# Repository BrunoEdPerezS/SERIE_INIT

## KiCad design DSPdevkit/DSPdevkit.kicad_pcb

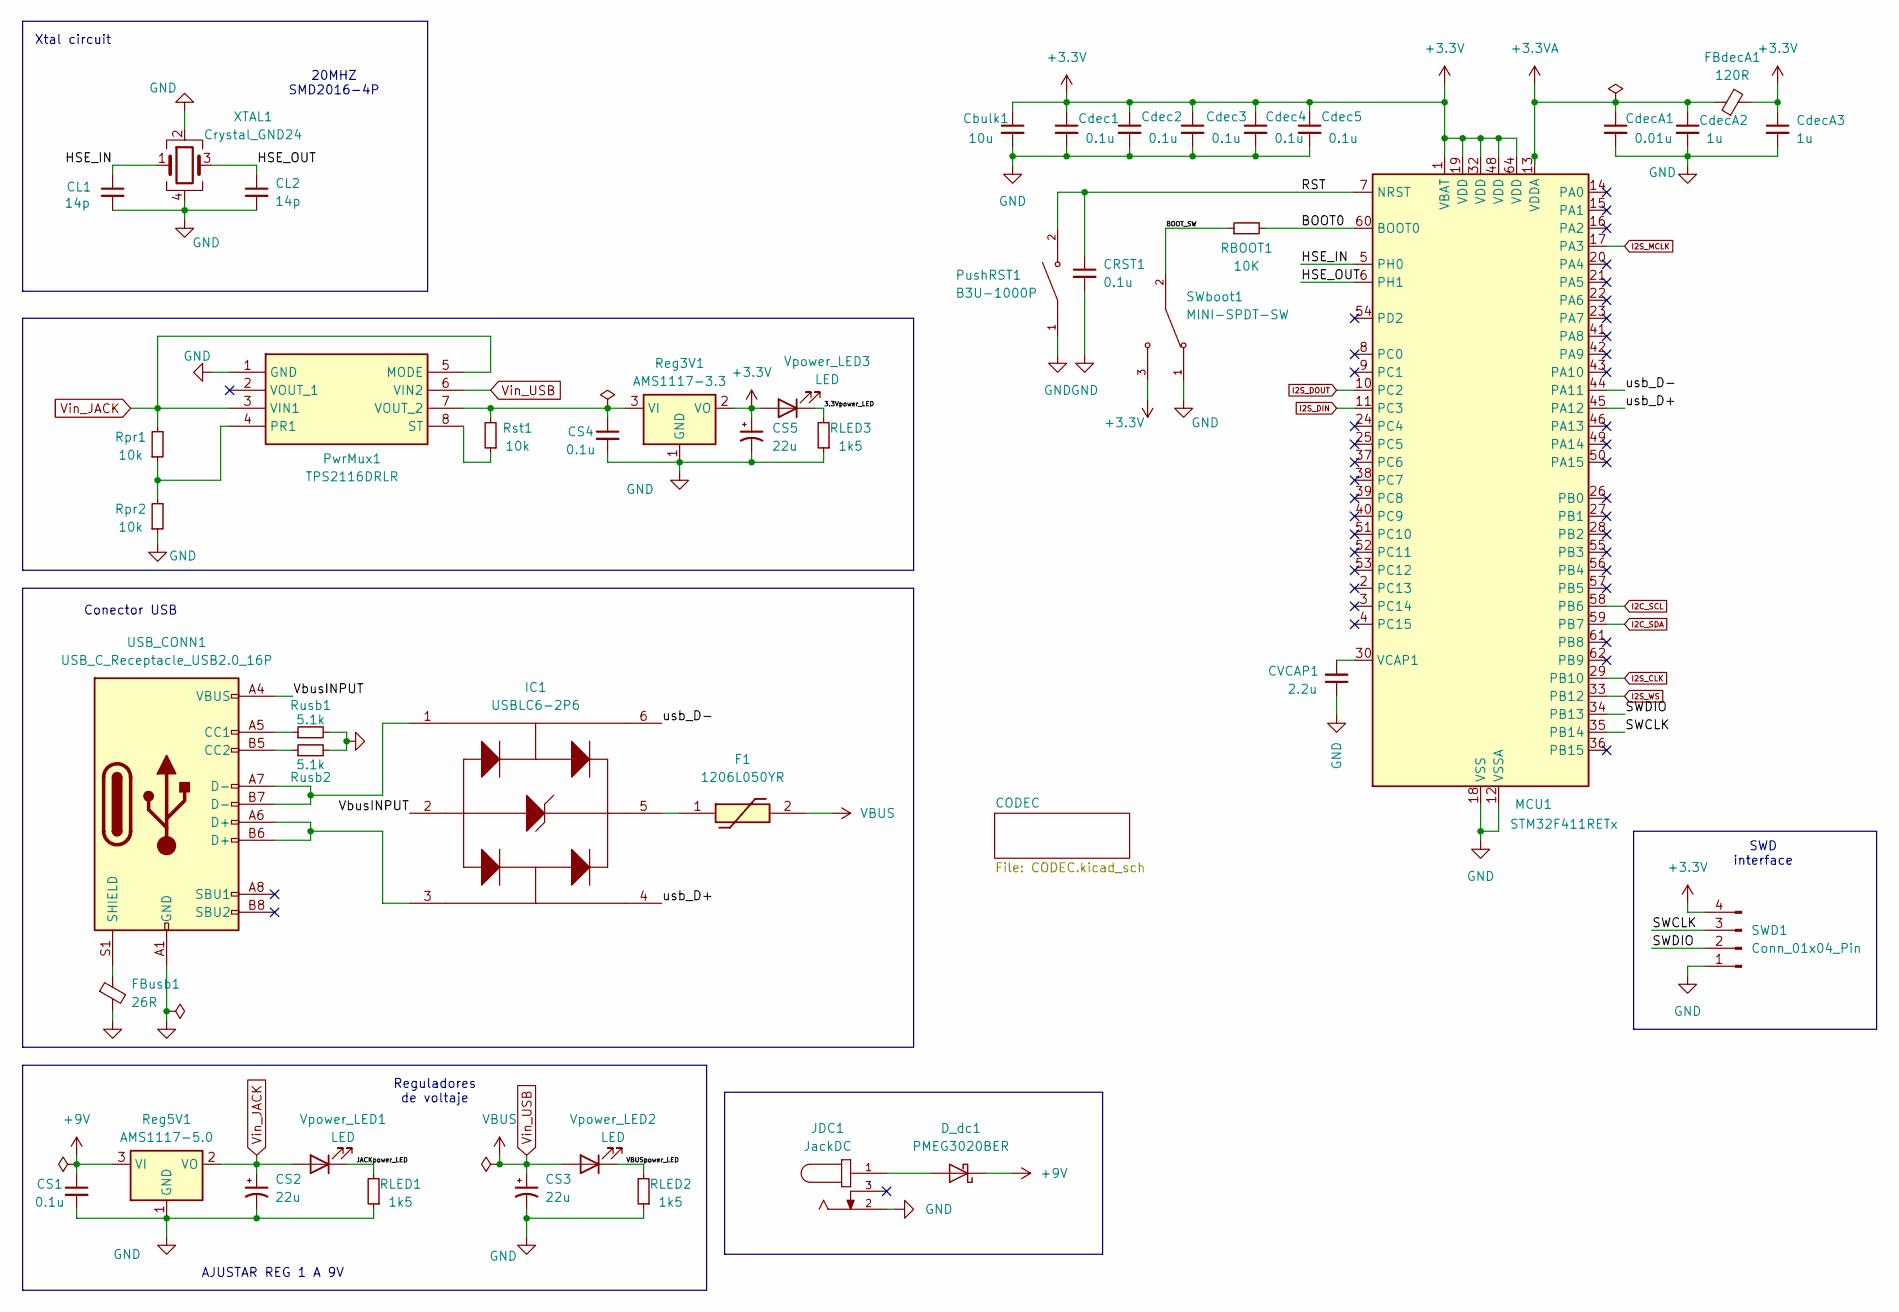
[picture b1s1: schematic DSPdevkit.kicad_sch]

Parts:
CL1, CL2: 14p; C_0402_1005Metric_Pad0.74x0.62mm_HandSolder
CRST1: 0.1u; C_0402_1005Metric_Pad0.74x0.62mm_HandSolder
CS1, CS4: 0.1u; C_1206_3216Metric_Pad1.33x1.80mm_HandSolder
CS2, CS3, CS5: 22u; CP_Elec_6.3x5.4
CVCAP1: 2.2u; C_1206_3216Metric_Pad1.33x1.80mm_HandSolder
Cbulk1: 10u; C_0805_2012Metric_Pad1.18x1.45mm_HandSolder
Cdec1, Cdec2, Cdec3, Cdec4, Cdec5: 0.1u; C_0402_1005Metric_Pad0.74x0.62mm_HandSolder
CdecA1: 0.01u; C_0402_1005Metric_Pad0.74x0.62mm_HandSolder
CdecA2, CdecA3: 1u; C_0402_1005Metric_Pad0.74x0.62mm_HandSolder
D_dc1: PMEG3020BER; Nexperia_CFP3_SOD-123W
F1: 1206L050YR; 1206L05015YR; Mouser Part Number 576-1206L050YR
FBdecA1: 120R; L_0603_1608Metric_Pad1.05x0.95mm_HandSolder
FBusb1: 26R; L_0603_1608Metric_Pad1.05x0.95mm_HandSolder
IC1: USBLC6-2P6; USBLC62P6; Mouser Part Number 511-USBLC6-2P6
JDC1: JackDC; GCT_DCJ200-10-A-XX-K_REVA; PARTREV A
MCU1: STM32F411RETx; LQFP-64_10x10mm_P0.5mm
PushRST1: B3U-1000P; SW_SPST_B3U-1000P
PwrMux1: TPS2116DRLR; SOTFL50P160X60-8N; Mouser Part Number 595-TPS2116DRLR
RBOOT1: 10K; R_1206_3216Metric_Pad1.30x1.75mm_HandSolder
RLED1, RLED2, RLED3: 1k5; R_1206_3216Metric_Pad1.30x1.75mm_HandSolder
Reg3V1: AMS1117-3.3; SOT-223-3_TabPin2
Reg5V1: AMS1117-5.0; SOT-223-3_TabPin2
Rpr1, Rpr2: 10k; R_1206_3216Metric_Pad1.30x1.75mm_HandSolder
Rst1: 10k; R_1206_3216Metric_Pad1.30x1.75mm_HandSolder
Rusb1, Rusb2: 5.1k; R_1206_3216Metric_Pad1.30x1.75mm_HandSolder
SWD1: Conn_01x04_Pin; PinHeader_1x04_P1.00mm_Vertical
SWboot1: MINI-SPDT-SW; SW_MINI-SPDT-SW; PARTREV C
USB_CONN1: USB_C_Receptacle_USB2.0_16P; USB_C_Receptacle_GCT_USB4105-xx-A_16P_TopMnt_Horizontal
Vpower_LED1, Vpower_LED2, Vpower_LED3: LED; LED_1206_3216Metric_Pad1.42x1.75mm_HandSolder
XTAL1: Crystal_GND24; Crystal_SMD_2016-4Pin_2.0x1.6mm

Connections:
+3.3V: CS5.1, Cbulk1.1, Cdec1.1, Cdec2.1, Cdec3.1, Cdec4.1, Cdec5.1, CdecA3.1, FBdecA1.2, MCU1.1 (VBAT), MCU1.19 (VDD), MCU1.32 (VDD), MCU1.48 (VDD), MCU1.64 (VDD), Reg3V1.2 (VO), SWD1.4, SWboot1.3, Vpower_LED3.2 (A); also elsewhere on the board
+3.3VA: CdecA1.1, CdecA2.1, FBdecA1.1, MCU1.13 (VDDA)
+9V: CS1.1, D_dc1.1 (K), Reg5V1.3 (VI)
/3.3Vpower_LED: RLED3.2, Vpower_LED3.1 (K)
/BOOT0: MCU1.60 (BOOT0), RBOOT1.2
/BOOT_SW: RBOOT1.1, SWboot1.2
/HSE_IN: CL1.1, MCU1.5 (PH0), XTAL1.1
/HSE_OUT: CL2.1, MCU1.6 (PH1), XTAL1.3
/JACKpower_LED: RLED1.2, Vpower_LED1.1 (K)
/RST: CRST1.1, MCU1.7 (NRST), PushRST1.2
/SWCLK: MCU1.35 (PB14), SWD1.3
/SWDIO: MCU1.34 (PB13), SWD1.2
/VBUSpower_LED: RLED2.2, Vpower_LED2.1 (K)
/VbusINPUT: IC1.2 (GND), USB_CONN1.A4 (VBUS), USB_CONN1.A9 (VBUS), USB_CONN1.B4 (VBUS), USB_CONN1.B9 (VBUS)
/usb_D+: IC1.4 (I/O2_2), MCU1.45 (PA12)
/usb_D-: IC1.6 (I/O1_2), MCU1.44 (PA11)
GND: CL1.2, CL2.2, CRST1.2, CS1.2, CS2.2, CS3.2, CS4.2, CS5.2, CVCAP1.1, Cbulk1.2, Cdec1.2, Cdec2.2, Cdec3.2, Cdec4.2, Cdec5.2, CdecA1.2, CdecA2.2, CdecA3.2, FBusb1.2, JDC1.2, MCU1.12 (VSSA), MCU1.18 (VSS), MCU1.31 (VSS), MCU1.47 (VSS), MCU1.63 (VSS), PushRST1.1, PwrMux1.1 (GND), RLED1.1, RLED2.1, RLED3.1, Reg3V1.1 (GND), Reg5V1.1 (GND), Rpr2.1, Rusb1.2, Rusb2.2, SWD1.1, SWboot1.1, USB_CONN1.A1 (GND), USB_CONN1.A12 (GND), USB_CONN1.B1 (GND), USB_CONN1.B12 (GND), XTAL1.2, XTAL1.4; also elsewhere on the board
I2C_SCL: MCU1.58 (PB6); also elsewhere on the board
I2C_SDA: MCU1.59 (PB7); also elsewhere on the board
I2S_CLK: MCU1.29 (PB10); also elsewhere on the board
I2S_DIN: MCU1.11 (PC3); also elsewhere on the board
I2S_DOUT: MCU1.10 (PC2); also elsewhere on the board
I2S_MCLK: MCU1.17 (PA3); also elsewhere on the board
I2S_WS: MCU1.33 (PB12); also elsewhere on the board
unnamed: D_dc1.2 (A), JDC1.1
unnamed: IC1.1 (I/O1_1), USB_CONN1.A7 (D-), USB_CONN1.B7 (D-)
unnamed: IC1.3 (I/O2_1), USB_CONN1.A6 (D+), USB_CONN1.B6 (D+)
unnamed: F1.1, IC1.5 (VBUS)
unnamed: CVCAP1.2, MCU1.30 (VCAP1)
unnamed: PwrMux1.4 (PR1), Rpr1.1, Rpr2.2
unnamed: PwrMux1.8 (ST), Rst1.1
unnamed: CS4.1, PwrMux1.7 (VOUT_2), Reg3V1.3 (VI), Rst1.2
unnamed: Rusb1.1, USB_CONN1.A5 (CC1)
unnamed: Rusb2.1, USB_CONN1.B5 (CC2)
unnamed: FBusb1.1, USB_CONN1.S1 (SHIELD)
Vin_JACK: CS2.1, PwrMux1.3 (VIN1), PwrMux1.5 (MODE), Reg5V1.2 (VO), Rpr1.2, Vpower_LED1.2 (A)
Vin_USB: CS3.1, F1.2, PwrMux1.6 (VIN2), Vpower_LED2.2 (A)

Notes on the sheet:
Conector USB
Xtal circuit
Reguladores de voltaje
SWD interface
AJUSTAR REG 1 A 9V
20MHZ SMD2016-4P

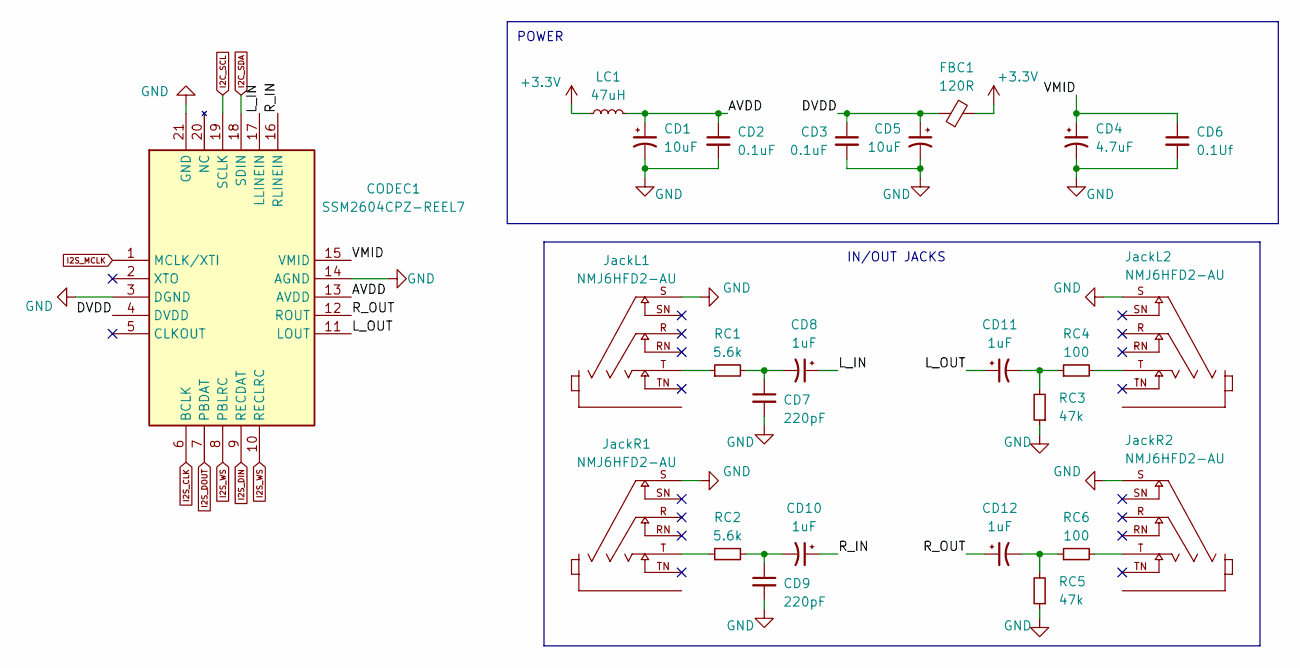
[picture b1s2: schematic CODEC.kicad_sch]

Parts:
CD1, CD5: 10uF; CP_Elec_6.3x5.4
CD2, CD3: 0.1uF; C_0402_1005Metric_Pad0.74x0.62mm_HandSolder
CD4: 4.7uF; CP_Elec_6.3x5.4
CD6: 0.1Uf; C_0402_1005Metric_Pad0.74x0.62mm_HandSolder
CD7, CD9: 220pF; C_0402_1005Metric_Pad0.74x0.62mm_HandSolder
CD8, CD10, CD11, CD12: 1uF; CP_Elec_3x5.4
CODEC1: SSM2604CPZ-REEL7; QFN50P400X400X80-21N-D; Mouser Part Number 584-SSM2604CPZ-R7
FBC1: 120R; L_0603_1608Metric_Pad1.05x0.95mm_HandSolder
JackL1, JackL2: NMJ6HFD2-AU; NEUTRIK_NMJ6HFD2-AU; PARTREV 26.02.2021
JackR1, JackR2: NMJ6HFD2-AU; NEUTRIK_NMJ6HFD2-AU; PARTREV 26.02.2021
LC1: 47uH; L_7.3x7.3_H3.5
RC1, RC2: 5.6k; R_1206_3216Metric_Pad1.30x1.75mm_HandSolder
RC3, RC5: 47k; R_1206_3216Metric_Pad1.30x1.75mm_HandSolder
RC4, RC6: 100; R_1206_3216Metric_Pad1.30x1.75mm_HandSolder

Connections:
+3.3V: FBC1.2, LC1.1; also elsewhere on the board
/CODEC/AVDD: CD1.1, CD2.1, CODEC1.13 (AVDD), LC1.2
/CODEC/DVDD: CD3.1, CD5.1, CODEC1.4 (DVDD), FBC1.1
/CODEC/L_IN: CD8.1, CODEC1.17 (LLINEIN)
/CODEC/L_OUT: CD11.1, CODEC1.11 (LOUT)
/CODEC/R_IN: CD10.1, CODEC1.16 (RLINEIN)
/CODEC/R_OUT: CD12.1, CODEC1.12 (ROUT)
/CODEC/VMID: CD4.1, CD6.1, CODEC1.15 (VMID)
GND: CD1.2, CD2.2, CD3.2, CD4.2, CD5.2, CD6.2, CD7.2, CD9.2, CODEC1.3 (DGND), CODEC1.14 (AGND), CODEC1.21 (GND), JackL1.S, JackL2.S, JackR1.S, JackR2.S, RC3.1, RC5.1; also elsewhere on the board
I2C_SCL: CODEC1.19 (SCLK); also elsewhere on the board
I2C_SDA: CODEC1.18 (SDIN); also elsewhere on the board
I2S_CLK: CODEC1.6 (BCLK); also elsewhere on the board
I2S_DIN: CODEC1.9 (RECDAT); also elsewhere on the board
I2S_DOUT: CODEC1.7 (PBDAT); also elsewhere on the board
I2S_MCLK: CODEC1.1 (MCLK/XTI); also elsewhere on the board
I2S_WS: CODEC1.8 (PBLRC), CODEC1.10 (RECLRC); also elsewhere on the board
unnamed: CD7.1, CD8.2, RC1.2
unnamed: CD9.1, CD10.2, RC2.2
unnamed: CD11.2, RC3.2, RC4.1
unnamed: CD12.2, RC5.2, RC6.1
unnamed: JackL1.T, RC1.1
unnamed: JackL2.T, RC4.2
unnamed: JackR1.T, RC2.1
unnamed: JackR2.T, RC6.2

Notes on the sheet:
IN/OUT JACKS
POWER

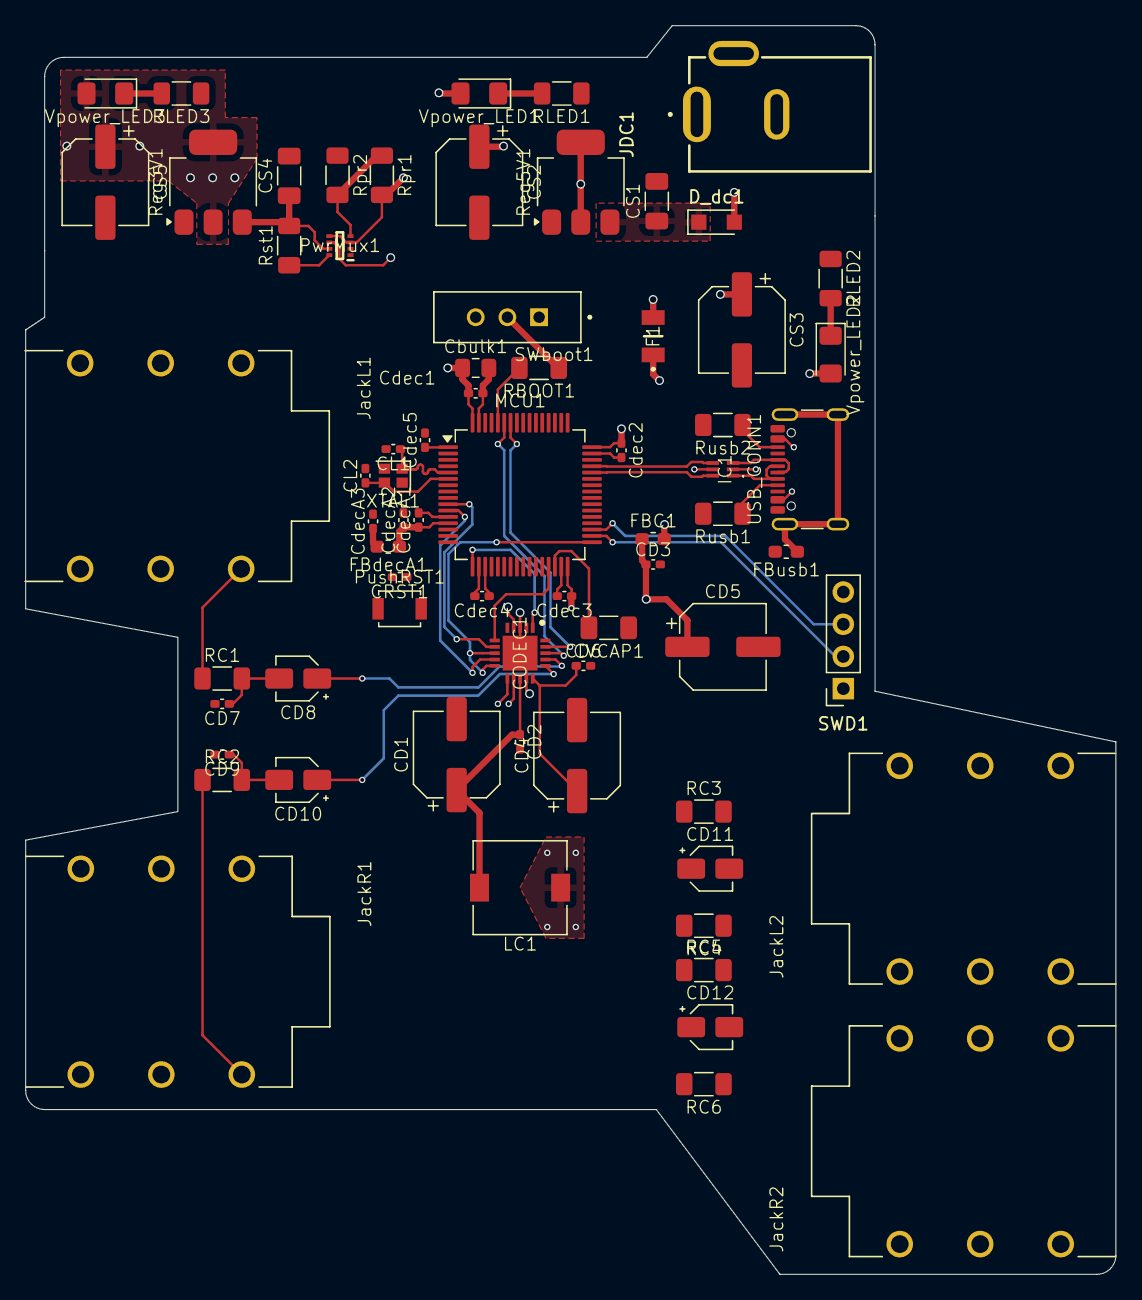
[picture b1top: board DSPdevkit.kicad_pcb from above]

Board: 4 copper layers, 86.0 x 98.5 mm, 70 parts (0 on the bottom side), 52 nets.

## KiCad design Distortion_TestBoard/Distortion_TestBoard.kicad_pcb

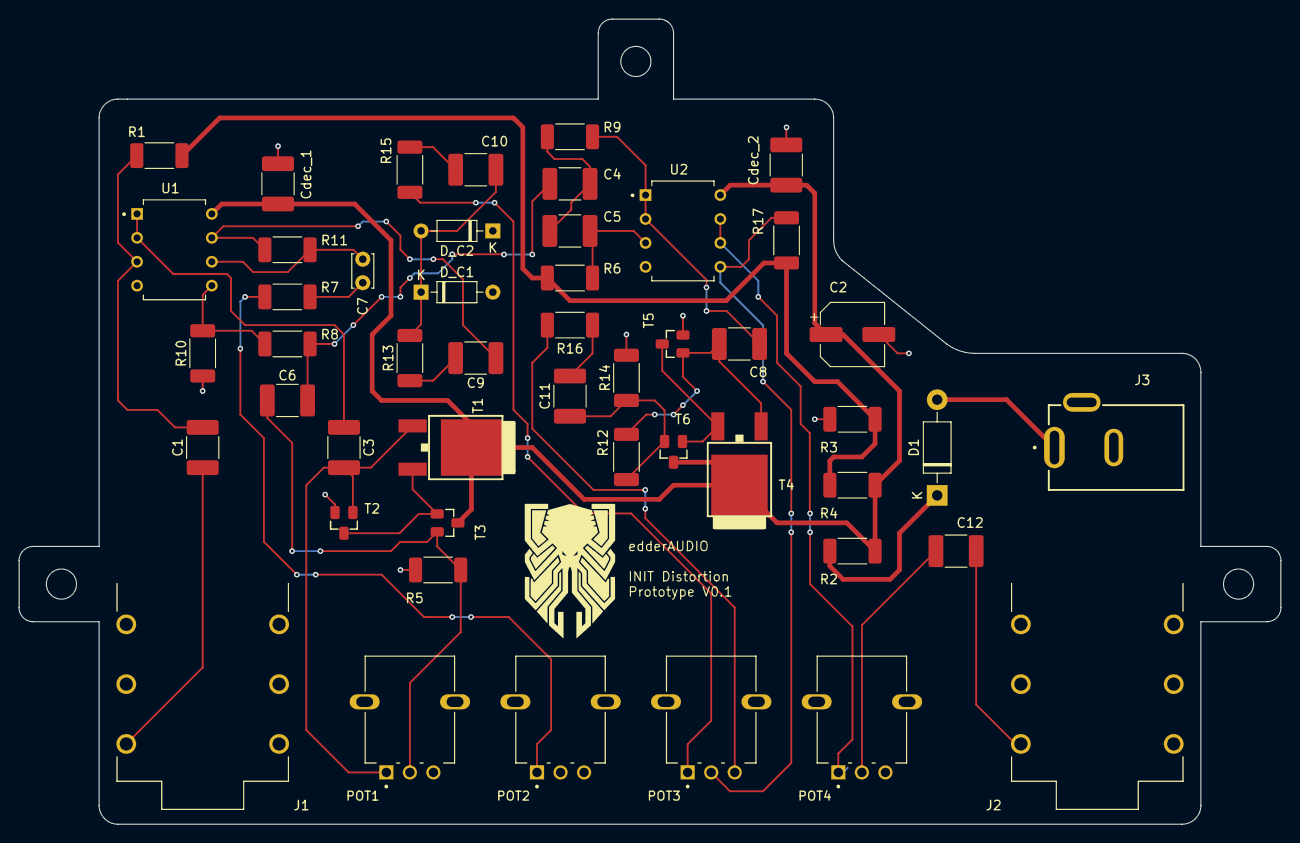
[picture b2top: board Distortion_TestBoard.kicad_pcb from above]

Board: 2 copper layers, 134.0 x 85.5 mm, 49 parts (0 on the bottom side), 33 nets.

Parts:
C1, C3, C6, C9, C10, C11, C12: 0.1u; C_1812_4532Metric_Pad1.57x3.40mm_HandSolder
C2: 100u; CP_Elec_6.3x5.4
C4, C5, C8: 0.01u; C_1812_4532Metric_Pad1.57x3.40mm_HandSolder
C7: 47n; C_Disc_D3.4mm_W2.1mm_P2.50mm
Cdec_1, Cdec_2: 0.01u; C_1812_4532Metric_Pad1.57x3.40mm_HandSolder
D1: 1N5817; D_DO-41_SOD81_P10.16mm_Horizontal
D_C1, D_C2: 1N914; D_DO-35_SOD27_P7.62mm_Horizontal
J1: Jack entrada; NEUTRIK_NMJ6HFD2-AU
J2: Jack salida; NEUTRIK_NMJ6HFD2-AU
J3: DC jack; GCT_DCJ200-10-A-XX-K_REVA
POT1, POT2: 500k; POT_RD901F-40-15R1-B100K-00DL1
POT3, POT4: 10K; POT_RD901F-40-15R1-B100K-00DL1
R1, R3, R4, R10, R17: 1M; R_2010_5025Metric_Pad1.40x2.65mm_HandSolder
R2: 47; R_2010_5025Metric_Pad1.40x2.65mm_HandSolder
R5, R14: R; R_2010_5025Metric_Pad1.40x2.65mm_HandSolder
R6, R9: 6.2k; R_2010_5025Metric_Pad1.40x2.65mm_HandSolder
R7: 50k; R_2010_5025Metric_Pad1.40x2.65mm_HandSolder
R8: 10K; R_2010_5025Metric_Pad1.40x2.65mm_HandSolder
R11, R12: 500k; R_2010_5025Metric_Pad1.40x2.65mm_HandSolder
R13: 330; R_2010_5025Metric_Pad1.40x2.65mm_HandSolder
R15, R16: 1k; R_2010_5025Metric_Pad1.40x2.65mm_HandSolder
T1, T4: FDD4141; TO252-DPAK
T2, T3, T5, T6: MMBF170; SOT23
U1, U2: TL072; TL072footprint

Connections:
4.5V: R1.1, R3.1, R4.1, R6.1, R17.1
+9V: C2.1, Cdec_1.1, Cdec_2.1, R2.1, R4.2, T1.2, T3.3, T4.2, T6.3, U1.8, U2.8
GND: C2.2, Cdec_1.2, Cdec_2.2, D_C1.2 (A), D_C2.1 (K), J1.R, J2.R, J3.2, POT2.2, POT4.3, R3.2, R5.2, R10.1, R14.2, T2.2, T5.2, U1.4, U2.4
HF_BOOST: C4.1, C6.2, R8.1
unnamed: C1.1, J1.T
unnamed: C3.2, POT1.1, T1.1, T2.1
unnamed: C4.2, C5.1, R9.2
unnamed: C6.1, POT1.2, R5.1, T3.2
unnamed: C7.1, R7.2
unnamed: C8.2, R12.1, T4.1, T5.1
unnamed: C9.2, R13.1
unnamed: C10.2, R15.1
unnamed: C11.1, R12.2, R14.1, T6.2
unnamed: C11.2, R16.1
unnamed: C12.1, POT4.2
unnamed: C12.2, J2.T
unnamed: D1.2 (A), J3.1
unnamed: D1.1 (K), R2.2
unnamed: C10.1, D_C1.1 (K), D_C2.2 (A), R13.2
unnamed: POT2.1, R7.1
unnamed: POT3.1, R15.2
unnamed: POT3.3, R16.2
unnamed: T1.3, T2.3, T3.1
unnamed: T4.3, T5.3, T6.1
unnamed: C1.2, R1.2, U1.3 (1IN+)
unnamed: C3.1, U1.1 (1OUT), U1.2 (1IN-)
unnamed: R8.2, R10.2, U1.5 (2IN+)
unnamed: C7.2, R11.1, U1.6 (2IN-)
unnamed: C9.1, R11.2, U1.7 (2OUT)
unnamed: C5.2, R6.2, U2.3 (1IN+)
unnamed: C8.1, R9.1, U2.1 (1OUT), U2.2 (1IN-)
unnamed: POT3.2, R17.2, U2.5 (2IN+)
unnamed: POT4.1, U2.6 (2IN-), U2.7 (2OUT)

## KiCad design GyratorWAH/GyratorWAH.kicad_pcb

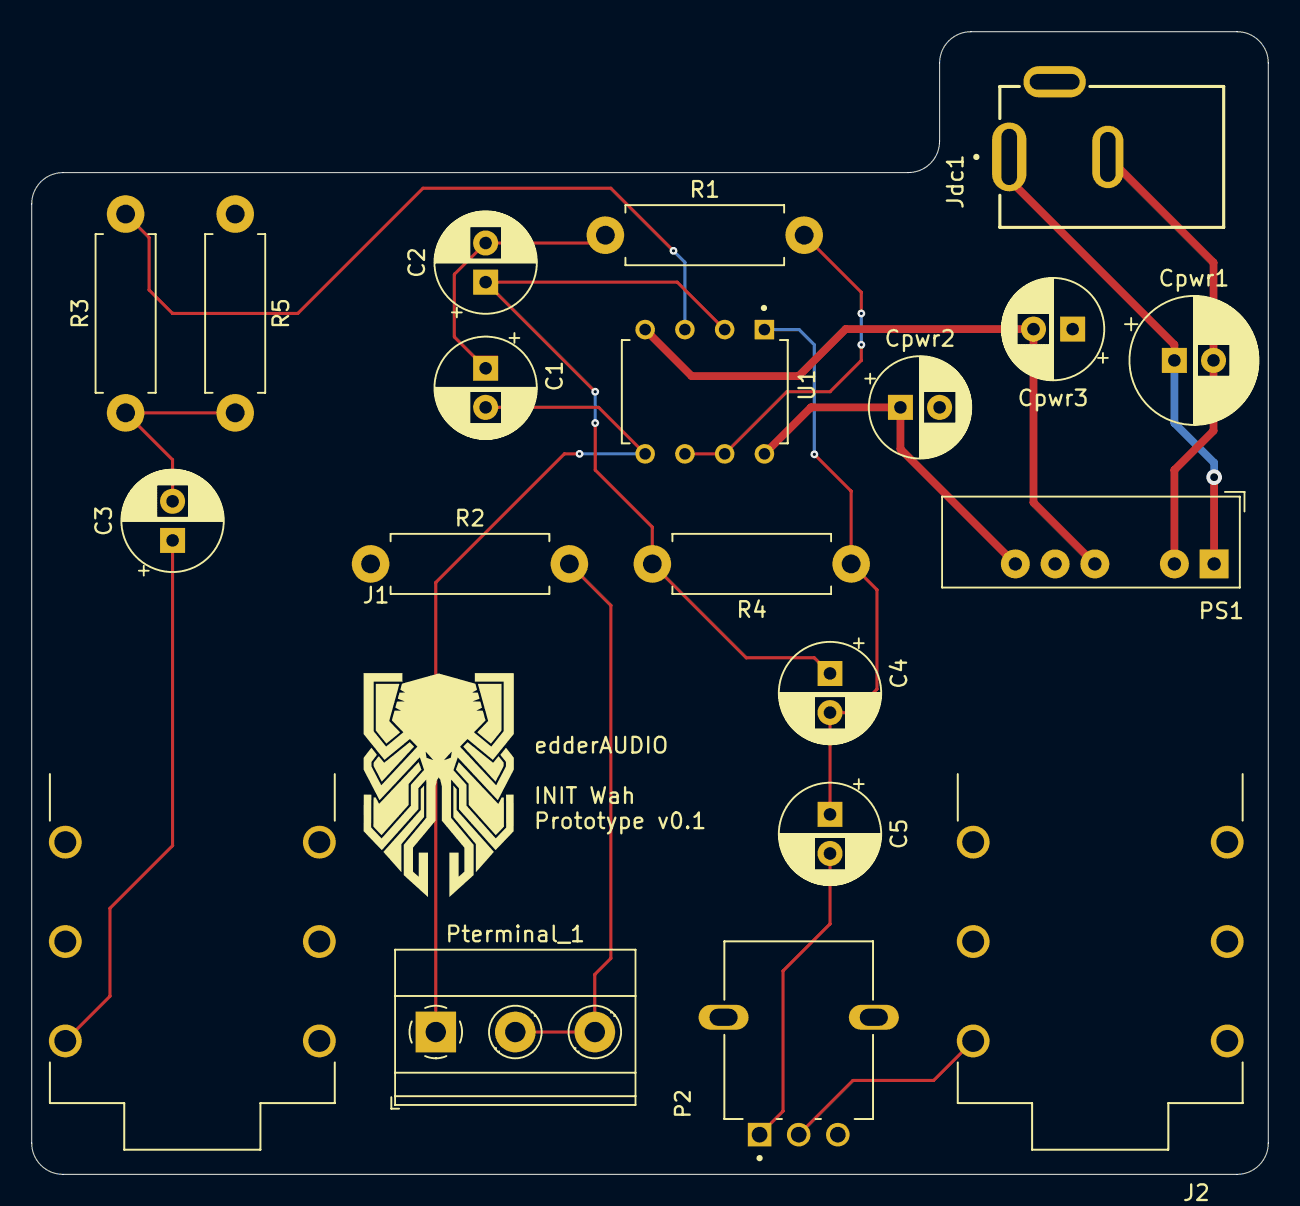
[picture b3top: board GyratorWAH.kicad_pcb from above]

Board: 2 copper layers, 79.0 x 73.0 mm, 20 parts (0 on the bottom side), 16 nets.

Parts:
C1, C2: 0.47u; CP_Radial_D6.3mm_P2.50mm
C3, C4: 0.1u; CP_Radial_D6.3mm_P2.50mm
C5: 10u; CP_Radial_D6.3mm_P2.50mm
Cpwr1: 100u; CP_Radial_D8.0mm_P2.50mm
Cpwr2, Cpwr3: 2.2u; CP_Radial_D6.3mm_P2.50mm
J1: Input Jack; NEUTRIK_NMJ6HFD2-AU
J2: Output jack; NEUTRIK_NMJ6HFD2-AU
Jdc1: DC 9V; GCT_DCJ200-10-A-XX-K_REVA
P2: 10K; POT_RD901F-40-15R1-B100K-00DL1
PS1: IA1209S; Converter_DCDC_XP_POWER-IAxxxxS_THT
Pterminal_1: Screw_Terminal_01x03; TerminalBlock_Phoenix_MKDS-1,5-3-5.08_1x03_P5.08mm_Horizont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
R1: 100; R_Axial_DIN0411_L9.9mm_D3.6mm_P12.70mm_Horizontal
R2: 220; R_Axial_DIN0411_L9.9mm_D3.6mm_P12.70mm_Horizontal
R3: 270k; R_Axial_DIN0411_L9.9mm_D3.6mm_P12.70mm_Horizontal
R4, R5: 10k; R_Axial_DIN0411_L9.9mm_D3.6mm_P12.70mm_Horizontal
U1: TL072; TL072footprint

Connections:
+12V: Cpwr2.1, PS1.6 (+Vout), U1.8
-12V: Cpwr3.2, PS1.4 (-Vout), U1.4
GND: Cpwr2.2, Cpwr3.1, J1.R, J2.R, P2.3, PS1.5 (0V), R2.1, R5.1
unnamed: C1.1, C2.2, R1.1
unnamed: C3.1, J1.T
unnamed: C3.2, R3.1, R5.2
unnamed: C5.2, P2.1
unnamed: J2.T, P2.2
unnamed: Cpwr1.1, Jdc1.1, PS1.1 (+Vin)
unnamed: Cpwr1.2, Jdc1.2, PS1.2 (-Vin)
unnamed: C1.2, Pterminal_1.1, U1.5 (2IN+)
unnamed: Pterminal_1.2, Pterminal_1.3, R2.2
unnamed: R3.2, U1.3 (1IN+)
unnamed: C2.1, C4.1, R4.2, U1.2 (1IN-)
unnamed: C4.2, C5.1, R4.1, U1.1 (1OUT)
unnamed: R1.2, U1.6 (2IN-), U1.7 (2OUT)

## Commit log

2024-05-12 Serie INIT Lista
